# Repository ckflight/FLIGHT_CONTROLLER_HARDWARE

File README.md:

# FLIGHT_CONTROLLER_HARDWARE

This is the first Flight_Controller Board i designed a few years ago with Atmel SAM3X8E ARM Cortex M3, BNO055 Orientation Sensor, TPA2012D Audio Amplifier, CC2541 Bluetooth IC, 4 Channel PWM input for radio interface (no SBUS input is available on this version), Microcard Interface for data logging and ESC PWM pins. Board is tested on a Quadcopter and it is working fine.

CC2541 IC can be flashed with HM10 firmware for the simplicity if you do not want to implement your own 8051 code in it.

It can be used with Arduino IDE for simple test and implementation.

50 Ohm impedance microstrip transmission line is making 0.342mm trace width with below stackup.

2 x 1W Stereo Speaker can be connected to the Audio Amplifier.

Since this was my first flight controller board design, i did not added a good stand alone gyro sensor. Instead used BNO055 since it provides both Euler Angle and Gyroscope Accelerometer and Magnetometer results.

Stackup layer information can be found here: https://docs.oshpark.com/services/four-layer/

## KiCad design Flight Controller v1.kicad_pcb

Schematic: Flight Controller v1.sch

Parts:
C1, C2, C21, C22, C23, C24, C25, C40, C41, C48, C49: 15pF; SMD_0402
C3, C8, C14, C17, C20, C27, C28, C29, C30, C31, C32, C33, C34, C36, C38, C39, C47, C52, C53, C55, C57: 100nF; SMD_0402
C4, C5: 47nF; SMD_0402
C6, C13, C35, C37: 10uF; SMD_0603
C7, C18, C19: 22uF; SMD_0805
C9, C10, C11, C12, C45, C51, C56: 1uF; SMD_0402
C15, C26: 10nF; SMD_0402
C16: 22pF; SMD_0402
C42: 1nF; SMD_0402
C43, C44: 18pF; SMD_0402
C46, C50, C54: 1pF; SMD_0402
D1: B230A; Diode_B230A
D2: USB_Led; Diode_0603
D3: Battery_Led; Diode_0603
D4: CC2541_LED; Diode_0603
D5: 1N4148WS; Diode_SOD-323
F1: Fuse; SMD_0603
J1: BatteryConnector; PinHeader_1x2-2.54mm
J2: USB_MicroB; USB_MicroB-TH
J3: AUDIO_OUT_L; PinHeader_1x2-2.54mm
J4: AUDIO_OUT_R; PinHeader_1x2-2.54mm
J5: JTAG-SWD
J6: CC2541_FLASHER; PinHeader_1x5-2.54mm
J7: MOTOR1; PinHeader_1x3-2.54mm
J8: 2.4GHz_CH4; PinHeader_1x3-2.54mm
J9: MOTOR2; PinHeader_1x3-2.54mm
J10: 2.4GHz_CH3; PinHeader_1x3-2.54mm
J11: ULTRASONIC; PinHeader_2x2-2.54mm
J12: MOTOR3; PinHeader_1x3-2.54mm
J13: 2.4GHz_CH2; PinHeader_1x3-2.54mm
J14: MOTOR4; PinHeader_1x3-2.54mm
J15: 2.4GHz_CH1; PinHeader_1x3-2.54mm
L1, L4: MAF1608GAD471CT0; SMD_0603
L2: 2.2uH; SMD_0805
L3: 4.7uH; SMD_1210
L5, L6, L7, L8: MH2029-330Y; SMD_0805
L9, L10: 2nH; SMD_0402
L11: 1nH; SMD_0402
L12: 3nH; SMD_0402
Q1: BSS138
R1, R2: 100; SMD_0402
R3, R8, R18, R19, R24, R26, R28: 1.5K; SMD_0402
R4: 470K; SMD_0402
R5, R10, R11, R17, R20, R21, R22, R23, R25: 105K; SMD_0402
R6, R12, R27: 52.3K; SMD_0402
R7, R9, R13: 10.2K; SMD_0402
R14, R15: 39; SMD_0402
R16: 6.8K; SMD_0402
SW1: RESET; Button_B3U-1000P
SW2: ERASE; Button_B3U-1000P
U1: AP3211; SOT23-6
U2: AP3429; SOT23-5
U3: BNO055; LGA-28_4x5mm-Pitch0.5mm
U4: TPA2012D; QFN20-1EXP_4x4mm-Pitch0.5mm
U5, U6: Connector_Pad-2
U7: SAM3X8E; LQFP-144_20x20mm-Pitch0.5mm
U8: MicroSD_Card; MicroSD_DM3AT-SF-PEJM5
U9: CC2541; QFN40-1EXP_6x6mm-Pitch0.5mm
U10: TXB0104RGYR; VQFN14-1EXP_4x4mm-Pitch0.5mm
U11: Buzzer; Buzzer_CSS-057SA
U12: SMA_Connector
Y1, Y3, Y4: 32.768KHz; ABS05_32.768KHz
Y2: 12MHz; Crystal_3.2mm-2.5mm
Y5: 32MHz; Crystal_2mm-1.6mm

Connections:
+3V3: C3.1, C16.1, C18.1, C26.1, C27.1, C29.1, C30.1, C31.1, C32.1, C33.1, C34.1, C35.1, C37.1, C47.2, C51.2, C52.2, C53.2, C55.2, C56.2, C57.2, D5.1 (K), J5.1, J6.1, L2.2, L5.1, L6.1, L8.1, R4.1, R9.2, R17.1, R18.2, R19.2, R20.1, R21.1, R22.1, R23.1, R25.1, SW2.2, U3.3 (VDD), U3.4 (NBOOT), U3.28 (VDDIO), U7.11 (VDDIO), U7.52 (VDDBU), U7.57 (VDDIN), U7.62 (VDDIO), U7.105 (VDDIO), U7.125 (VDDIO), U8.4 (VDD), U9.10 (DVDD2), U9.21 (AVDD5), U9.24 (AVDD3), U9.27 (AVDD2), U9.28 (AVDD1), U9.29 (AVDD4), U9.31 (AVDD6), U9.39 (DVVD1), U10.1 (VCCA), U10.8 (OE), U11.1 (+); also elsewhere on the board
+5V: C7.1, C13.2, C14.1, C19.1, D2.2 (A), F1.2, J8.2, J10.2, J11.2, J13.2, J15.2, L1.2, L3.2, R6.1, U2.1 (EN), U2.4 (VIN), U4.3 (PVDD), U4.7 (SHUTDOWN_L), U4.8 (SHUTDOWN_R), U4.13 (PVDD), U5.1, U6.2, U10.14 (VCCB); also elsewhere on the board
+VBattery: C6.1, D3.2 (A), J1.1, R12.1, U1.4 (EN), U1.5 (IN); also elsewhere on the board
AVDD: C8.2, L1.1, U4.9 (AVDD)
BNO_INT: U3.14 (INT), U7.143 (PB24)
BNO_RESET: R9.1, U3.11 (RESET), U7.144 (PB25)
BUZZER: R28.1, U7.136 (PC25)
CC2541_KEY: U7.13 (PD0), U9.7 (P1_3)
CC2541_PIN7: J6.3, U9.34 (P2_2)
CC2541_PIN8: J6.4, U9.35 (P2_1)
CC2541_RESET: C42.1, J6.5, R26.1, U7.15 (PD2)
D+: J2.3 (D+), R15.1, U7.37 (DHSDP)
D-: J2.2 (D-), R14.1, U7.38 (DHSDM)
DAC0: R1.1, R2.1, U7.76 (PB15)
ESC1: J7.1, U7.132 (PC21)
ESC2: J9.1, U7.133 (PC22)
ESC3: J12.1, U7.134 (PC23)
ESC4: J14.1, U7.135 (PC24)
GND: C1.2, C2.2, C3.2, C6.2, C7.2, C13.1, C14.2, C17.1, C18.2, C19.2, C20.1, C21.2, C22.2, C23.2, C24.2, C25.2, C27.2, C28.2, C29.2, C30.2, C31.2, C32.2, C33.2, C34.2, C35.2, C36.2, C37.2, C38.2, C39.2, C40.2, C41.2, C42.2, C45.1, C46.1, C47.1, C48.1, C49.1, C51.1, C52.1, C53.1, C54.1, C55.1, C56.1, C57.1, D1.2 (A), D4.1 (K), J1.2, J2.5 (GND), J5.3, J5.5, J5.9, J6.2, J7.3, J8.3, J9.3, J10.3, J11.4, J12.3, J13.3, J14.3, J15.3, L4.2, L9.1, Q1.2 (S), R3.1, R5.2, R7.2, R8.1, R10.2, R11.2, R13.2, R16.2, R27.2, SW1.1, U1.2 (GND), U2.2 (GND), U3.2 (GND), U3.5 (PS1), U3.6 (PS0), U3.10 (BL_IND), U3.15 (PIN15), U3.16 (PIN16), U3.17 (COM3/I2CADR), U3.18 (COM2/GND), U3.25 (GND), U4.4 (PGND), U4.12 (PGND), U4.21 (THERMAL), U7.12 (GND), U7.33 (GNDPLL), U7.44 (GNDUTMI), U7.54 (GNDBU), U7.58 (GND), U7.74 (GNDANA), U7.106 (GND), U7.126 (GND), U8.6 (VSS), U8.10 (DETA), U8.11 (SHIELD), U9.1 (GND), U9.41 (GND/EXP), U10.7 (GND), U10.15 (EXP), U12.2, U12.3, U12.4, U12.5, Y2.2, Y2.4, Y5.2, Y5.4; also elsewhere on the board
GNDA: C4.2, C5.2, C8.1, C11.2, C12.2, C17.2, L4.1, U4.18 (AGND)
I2C_SCL: R19.1, U3.19 (SCL), U7.87 (PB13)
I2C_SDA: R18.1, U3.20 (SDA), U7.86 (PB12)
JTAG_TCK: J5.4, R21.2, U7.28 (PB28)
JTAG_TDI: J5.8, R22.2, U7.29 (PB29)
JTAG_TDO: J5.6, U7.30 (PB30)
JTAG_TMS: J5.2, R20.2, U7.31 (PB31)
MCU_RESET: C26.2, J5.10, R23.2, SW1.2, U7.47 (NRSTB); also elsewhere on the board
unnamed: C1.1, U3.27 (XIN32), Y1.1
unnamed: C2.1, U3.26 (XOUT32), Y1.2
unnamed: C4.1, C9.2, R1.2
unnamed: C9.1, U4.20 (INL+)
unnamed: C10.1, U4.16 (INR+)
unnamed: C5.1, C10.2, R2.2
unnamed: C11.1, U4.19 (INL-)
unnamed: C12.1, U4.17 (INR-)
unnamed: C15.1, U1.1 (BS)
unnamed: C15.2, D1.1 (K), L3.1, U1.6 (SW)
unnamed: C16.2, R4.2, R5.1, U2.5 (FB)
unnamed: C20.2, U3.9 (CAP)
unnamed: C21.1, U7.35 (XOUT), Y2.1
unnamed: C22.1, U7.36 (XIN), Y2.3
unnamed: C23.1, U7.49 (XOUT32), Y3.1
unnamed: C24.1, U7.48 (XIN32), Y3.2
unnamed: C25.1, R16.1, U7.40 (VBG)
unnamed: C28.1, L5.2, U7.75 (ADVREF)
unnamed: C38.1, L7.2, U7.34 (VDDPLL)
unnamed: C40.1, U9.33 (P2_3/XOSC32K_Q2), Y4.1
unnamed: C41.1, U9.32 (P2_4/XOSC32K_Q1), Y4.2
unnamed: C43.1, C50.2, L9.2
unnamed: C43.2, U9.25 (RF_P)
unnamed: C44.1, C46.2, L10.2
unnamed: C44.2, U9.26 (RF_N)
unnamed: C45.2, U9.40 (DCOUPL)
unnamed: C48.2, U9.22 (XOSC_Q1), Y5.3
unnamed: C49.2, U9.23 (XOSC_Q2), Y5.1
unnamed: C50.1, L10.1, L11.2
unnamed: C54.2, L11.1, L12.2
unnamed 57: D2.1 (K), R3.2; also elsewhere on the board
unnamed 58: D3.1 (K), R8.2; also elsewhere on the board
unnamed 59: D4.2 (A), R24.1; also elsewhere on the board
unnamed: D5.2 (A), Q1.3 (D), U11.2 (-)
unnamed: J3.1, U4.5 (OUTL-)
unnamed: J3.2, U4.2 (OUTL+)
unnamed: J4.1, U4.11 (OUTR-)
unnamed: J4.2, U4.14 (OUTR+)
unnamed: L2.1, U2.3 (LX)
unnamed: L7.1, U7.10 (VDDCORE), U7.45 (VDDCORE), U7.56 (VDDOUT), U7.61 (VDDCORE), U7.104 (VDDCORE), U7.124 (VDDCORE)
unnamed: L12.1, U12.1
unnamed: Q1.1 (G), R28.2
unnamed: R6.2, R7.1, U1.3 (FB)
unnamed: R10.1, U4.15 (G0), U5.2
unnamed: R11.1, U4.1 (G1), U6.1
unnamed: R12.2, R13.1, U7.85 (PA2)
unnamed: R14.2, U7.43 (DFSDM)
unnamed: R15.2, U7.42 (DFSDP)
unnamed: R17.2, U7.53 (FWUP)
unnamed: R24.2, U9.8 (P1_2)
unnamed: R26.2, U9.20 (NRESET)
unnamed: R27.1, U9.30 (RBIAS)
unnamed 85: SW2.1, U7.130 (PC0); also elsewhere on the board
RECEIVER_HV_1: J15.1, U10.10 (B4)
RECEIVER_HV_2: J13.1, U10.11 (B3)
RECEIVER_HV_3: J10.1, U10.12 (B2)
RECEIVER_HV_4: J8.1, U10.13 (B1)
RECEIVER_LV_1: U7.94 (PC12), U10.5 (A4)
RECEIVER_LV_2: U7.95 (PC13), U10.4 (A3)
RECEIVER_LV_3: U7.96 (PC14), U10.3 (A2)
RECEIVER_LV_4: U7.97 (PC15), U10.2 (A1)
RX: U7.27 (PA8), U9.38 (P1_6)
SDCARD_SS: R25.2, U7.111 (PA28), U8.2 (DAT3/CD)
SONIC_ECHO: J11.3, U7.22 (PD9)
SONIC_TRIGGER: J11.1, U7.14 (PD1)
SPI_MISO: U7.108 (PA25), U8.7 (DAT0)
SPI_MOSI: U7.109 (PA26), U8.3 (CMD)
SPI_SCK: U7.110 (PA27), U8.5 (CLK)
TX: U7.2 (PA9), U9.37 (P1_7)
VDDANA: C39.1, L8.2, U7.73 (VDDANA)
VDDUTMI: C36.1, L6.2, U7.41 (VDDUTMI)
VUSB: F1.1, J2.1 (VBUS), U7.39 (VBUS)

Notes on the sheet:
0x28 I2C Address
TX OF CC2541
RX OF CC2541
DET IS MECHANICAL SWITCH INDICATING WEATHER THE SD CARD INSERTED OR NOT SO NOT CONNECTING TO ANY GPIO

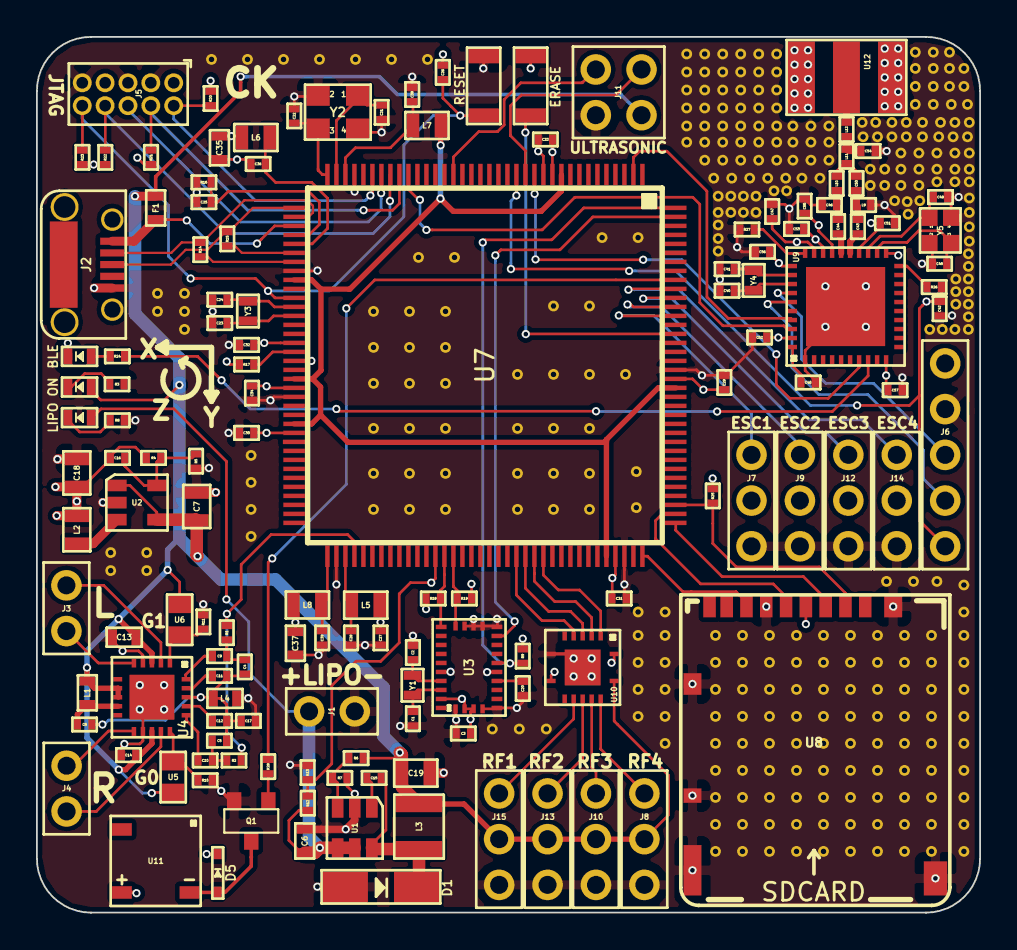
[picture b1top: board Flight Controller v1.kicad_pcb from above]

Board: 4 copper layers, 52.4 x 48.7 mm, 138 parts (0 on the bottom side), 99 nets.

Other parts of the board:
BLE: CC2541_LED; Diode_0603
ERASE: ERASE; Button_B3U-1000P
LIPO: Battery_Led; Diode_0603
ON: USB_Led; Diode_0603
RESET: RESET; Button_B3U-1000P

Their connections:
+3V3: ERASE.2; also elsewhere on the board
+5V: ON.2; also elsewhere on the board
+VBattery: LIPO.2; also elsewhere on the board
GND: BLE.1, RESET.1; also elsewhere on the board
MCU_RESET: RESET.2; also elsewhere on the board
unnamed 57: ON.1; also elsewhere on the board
unnamed 58: LIPO.1; also elsewhere on the board
unnamed 59: BLE.2; also elsewhere on the board
unnamed 85: ERASE.1; also elsewhere on the board
